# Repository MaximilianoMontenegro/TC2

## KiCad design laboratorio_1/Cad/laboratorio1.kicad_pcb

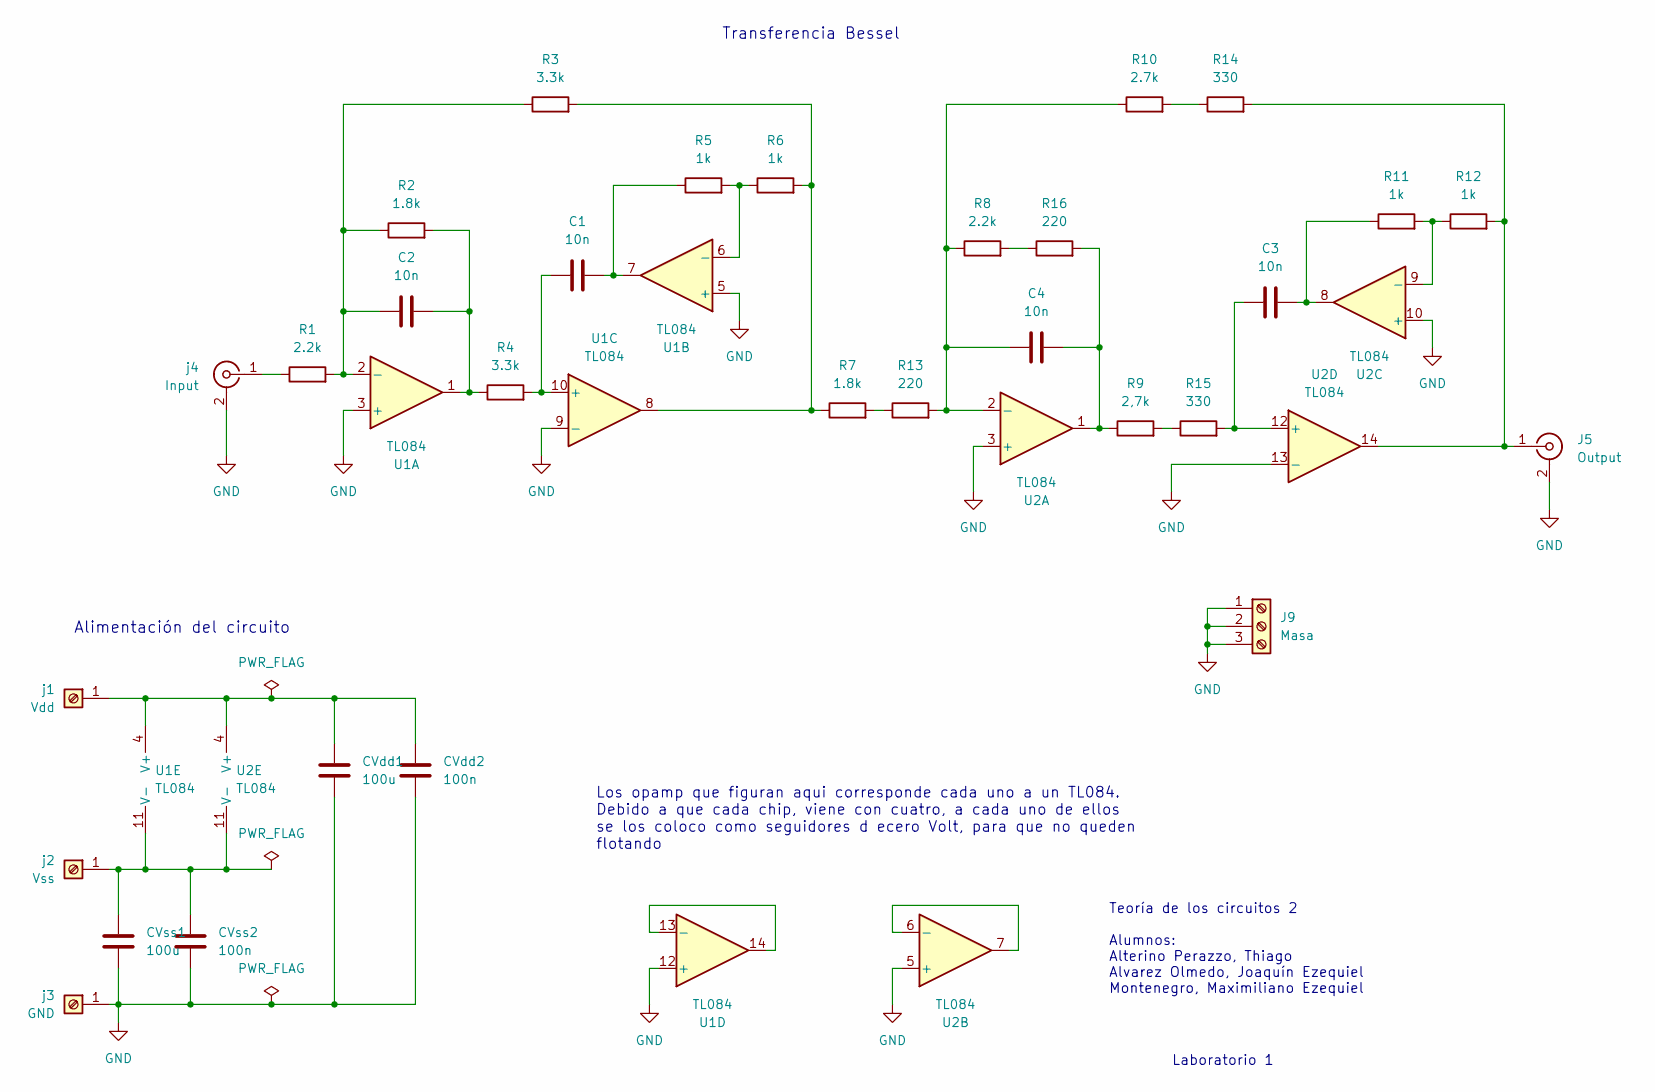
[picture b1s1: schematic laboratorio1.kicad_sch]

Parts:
C1, C2, C3, C4: 10n; C_Rect_L11.0mm_W3.4mm_P10.00mm_MKT
CVdd1: 100u; C_Radial_D8.0mm_H11.5mm_P3.50mm
CVdd2: 100n; C_Disc_D5.0mm_W2.5mm_P2.50mm
CVss1: 100u; C_Radial_D8.0mm_H11.5mm_P3.50mm
CVss2: 100n; C_Disc_D5.0mm_W2.5mm_P2.50mm
J5: Output; BNC_Amphenol_B6252HB-NPP3G-50_Horizontal
J9: Masa; PinHeader_1x03_P1.00mm_Vertical
R1, R8: 2.2k; R_Axial_DIN0207_L6.3mm_D2.5mm_P10.16mm_Horizontal
R2, R7: 1.8k; R_Axial_DIN0207_L6.3mm_D2.5mm_P10.16mm_Horizontal
R3, R4: 3.3k; R_Axial_DIN0207_L6.3mm_D2.5mm_P10.16mm_Horizontal
R5, R6, R11, R12: 1k; R_Axial_DIN0207_L6.3mm_D2.5mm_P10.16mm_Horizontal
R9: 2,7k; R_Axial_DIN0207_L6.3mm_D2.5mm_P10.16mm_Horizontal
R10: 2.7k; R_Axial_DIN0207_L6.3mm_D2.5mm_P10.16mm_Horizontal
R13, R16: 220; R_Axial_DIN0207_L6.3mm_D2.5mm_P10.16mm_Horizontal
R14, R15: 330; R_Axial_DIN0207_L6.3mm_D2.5mm_P10.16mm_Horizontal
U1, U2: TL084; CERDIP-14_W7.62mm_SideBrazed_LongPads_Socket
j1: Vdd; Banana_Jack_1Pin
j2: Vss; Banana_Jack_1Pin
j3: GND; Banana_Jack_1Pin
j4: Input; BNC_Amphenol_B6252HB-NPP3G-50_Horizontal

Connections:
GND: CVdd1.2, CVdd2.2, CVss1.2, CVss2.2, J5.2 (Ext), J9.1, J9.2, J9.3, U1.3 (+), U1.5 (+), U1.9 (-), U1.12 (+), U2.3 (+), U2.5 (+), U2.10 (+), U2.13 (-), j3.1, j4.2 (Ext)
unnamed: C1.2, R5.1, U1.7
unnamed: C2.2, R2.2, R4.1, U1.1
unnamed: C3.2, R11.1, U2.8
unnamed: C4.2, R9.1, R16.2, U2.1
unnamed: J5.1 (In), R12.2, R14.2, U2.14
unnamed: R3.2, R6.2, R7.1, U1.8
unnamed: R7.2, R13.1
unnamed: R9.2, R15.1
unnamed: R8.2, R16.1
unnamed: C2.1, R1.2, R2.1, R3.1, U1.2 (-)
unnamed: R5.2, R6.1, U1.6 (-)
unnamed: C1.1, R4.2, U1.10 (+)
unnamed: U1.13 (-), U1.14
unnamed: CVdd1.1, CVdd2.1, U1.4 (V+), U2.4 (V+), j1.1
unnamed: CVss1.1, CVss2.1, U1.11 (V-), U2.11 (V-), j2.1
unnamed: C4.1, R8.1, R10.1, R13.2, U2.2 (-)
unnamed: U2.6 (-), U2.7
unnamed: R11.2, R12.1, U2.9 (-)
unnamed: C3.1, R15.2, U2.12 (+)
unnamed: R1.1, j4.1 (In)

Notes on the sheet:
Transferencia Bessel
Alimentación del circuito
Laboratorio 1
Los opamp que figuran aqui corresponde cada uno a un TL084. Debido a que cada chip, viene con cuatro, a cada uno de ellos se los coloco como seguidores d ecero Volt, para que no queden flotando
Teoría de los circuitos 2 Alumnos: Alterino Perazzo, Thiago Alvarez Olmedo, Joaquín Ezequiel Montenegro, Maximiliano Ezequiel

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
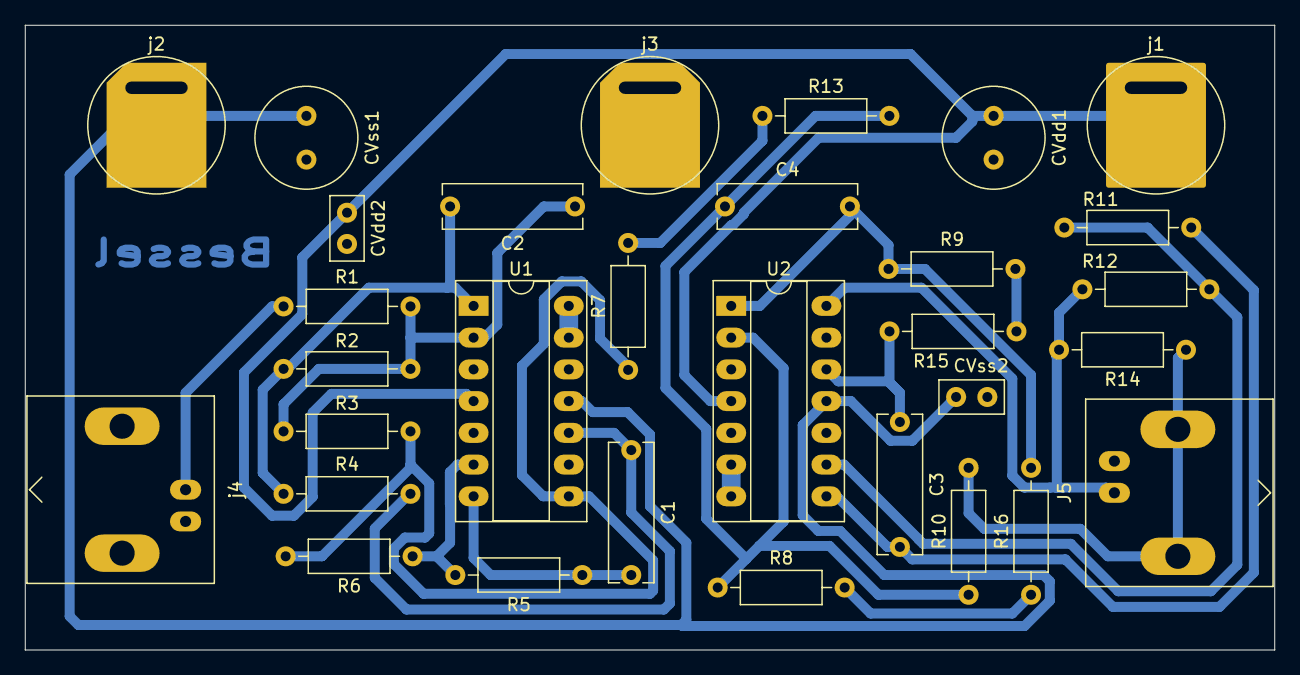
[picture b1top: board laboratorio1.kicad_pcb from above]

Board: 2 copper layers, 100.0 x 50.0 mm, 31 parts (0 on the bottom side), 22 nets.

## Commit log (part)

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2026-04-29 Primer commit limpio
2026-05-18 agrego notebook tarea 0
2026-05-19 Agrego tarea 1
2026-05-26 agrego tarea 2
2026-06-08 agrego tarea 3
2026-06-18 adjunto tarea4
2026-06-21 subo archivo de labo
2026-06-21 actualizo el jupyter
2026-06-22 Actualizacion laboratorio 1
2026-06-22 ultima actualización
2026-06-22 actualizacioón con letra manuscrita
2026-06-23 actualizo LTSpice, y Kicad
2026-06-23 ahora si actualizo con windows el kicad
2026-06-23 ggregue Jumper al Cad
2026-06-24 actualizo desde linux
2026-06-24 última actualización del get, modifcación completa del pcb
2026-06-24 version final
